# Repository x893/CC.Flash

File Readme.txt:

Implement Texas flash programming protocol via Arduino board.
See
http://www.ti.com/tool/cc-debugger
and
http://akb77.com/g/rf/program-cc-debugger-cc2511-with-arduino/
for details

1. Upload CC_Flash.pde sketch to Arduino
2. Connect
    Target          Arduino
        DC (P2.1) - pin 5
        DD (P2.2) - pin 6
        RST       - pin 7
        GND       - GND
3. Start program CC.Flash.exe (need .NET 2.0)

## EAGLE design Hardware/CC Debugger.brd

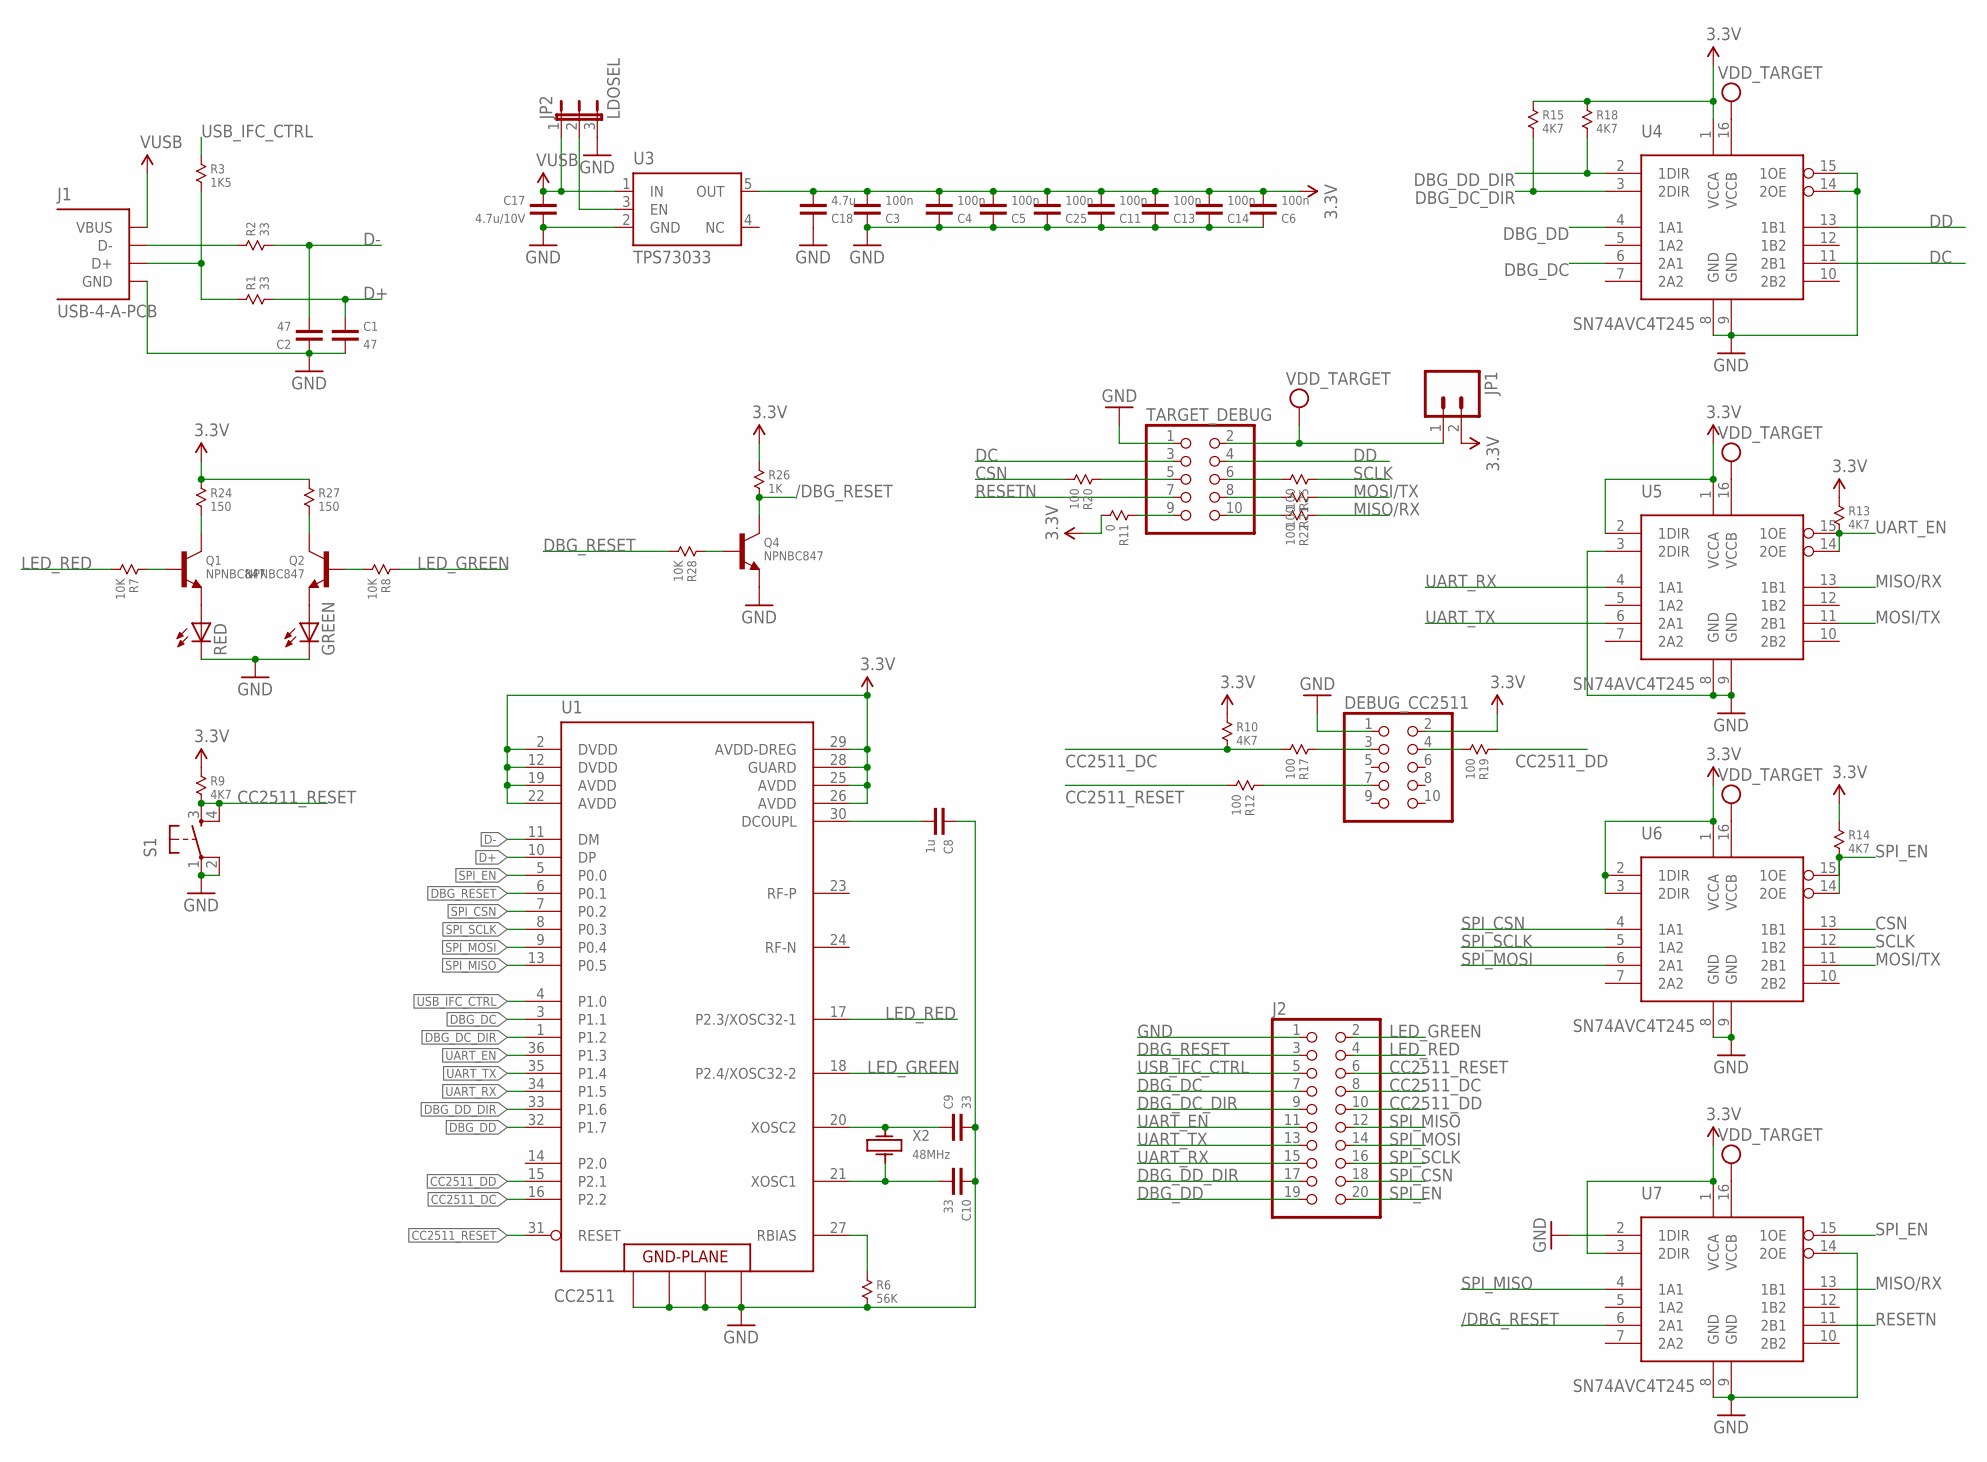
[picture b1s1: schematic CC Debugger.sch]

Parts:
C1, C2: 47; 0603
C3, C4, C5, C6, C11, C13, C14, C25: 100n; 0603
C8: 1u; 0603
C9, C10: 33; 0603
C17: 4.7u/10V; 0603
C18: 4.7u; 0603
DEBUG_CC2511: PINHD-2X5; 2X05
GREEN: LEDCHIPLED_0805; CHIPLED_0805
J1: USB-4-A-PCB; USB-A-PCB
J2: PINHD-2X10; 2X10
JP1: M02PTH; 1X02
JP2: LDOSEL; SJ_3
Q1, Q2, Q4: NPNBC847; SOT-23
R1, R2: 33; 0603
R3: 1K5; 0603
R6: 56K; 0603
R7, R8, R28: 10K; 0603
R9, R10, R13, R14, R15, R18: 4K7; 0603
R11: 0; 0603
R12, R17, R19, R20, R21, R22, R25: 100; 0603
R24, R27: 150; 0603
R26: 1K; 0603
RED: LEDCHIPLED_0805; CHIPLED_0805
S1: TAC_SWITCHPTH; TACTILE-PTH
TARGET_DEBUG: PINHD-2X5; 2X05
U1: CC2511; QLP-36
U3: TPS73033; SOT23-5
U4, U5, U6, U7: SN74AVC4T245; TSSOP16
X2: 48MHz; KX-9A

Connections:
3.3V: C3.1, C4.1, C5.1, C6.1, C11.1, C13.1, C14.1, C18.1, C25.1, DEBUG_CC2511.2, JP1.2, R9.1, R10.1, R11.2, R13.1, R14.1, R15.1, R18.1, R24.1, R26.1, R27.1, U1.2 (DVDD), U1.12 (DVDD), U1.19 (AVDD), U1.22 (AVDD), U1.25 (AVDD), U1.26 (AVDD), U1.28 (GUARD), U1.29 (AVDD-DREG), U3.5 (OUT), U4.1 (VCCA), U5.1 (VCCA), U5.2 (1DIR), U6.1 (VCCA), U6.2 (1DIR), U6.3 (2DIR), U7.1 (VCCA), U7.3 (2DIR)
5V: C17.2, J1.VUSB (VBUS), JP2.1, U3.1 (IN)
/DBG_RESET: Q4.3 (C), R26.2, U7.6 (2A1)
CC2511_DC: J2.8, R10.2, R17.2, U1.16 (P2.2)
CC2511_DD: J2.10, R19.1, U1.15 (P2.1)
CC2511_RESET: J2.6, R9.2, R12.2, S1.3, S1.4, U1.31 (RESET)
CSN: R20.2, U6.13 (1B1)
D+: C1.2, R1.2, U1.10 (DP)
D-: C2.1, R2.2, U1.11 (DM)
DBG_DC: J2.7, U1.3 (P1.1), U4.6 (2A1)
DBG_DC_DIR: J2.9, R15.2, U1.1 (P1.2), U4.3 (2DIR)
DBG_DD: J2.19, U1.32 (P1.7), U4.4 (1A1)
DBG_DD_DIR: J2.17, R18.2, U1.33 (P1.6), U4.2 (1DIR)
DBG_RESET: J2.3, R28.2, U1.6 (P0.1)
DC: TARGET_DEBUG.3, U4.11 (2B1)
DD: TARGET_DEBUG.4, U4.13 (1B1)
GND: C1.1, C2.2, C3.2, C4.2, C5.2, C6.2, C8.2, C9.1, C10.2, C11.2, C13.2, C14.2, C17.1, C18.2, C25.2, DEBUG_CC2511.1, GREEN.C, J1.GND, J2.1, JP2.3, Q4.2 (E), R6.2, RED.C, S1.1, S1.2, TARGET_DEBUG.1, U1.37 (GND), U1.38 (GND), U1.39 (GND), U1.40 (GND), U3.2 (GND), U4.8 (GND), U4.9 (GND), U4.14 (2OE), U4.15 (1OE), U5.3 (2DIR), U5.8 (GND), U5.9 (GND), U6.8 (GND), U6.9 (GND), U7.2 (1DIR), U7.8 (GND), U7.9 (GND), U7.14 (2OE)
LED_GREEN: J2.2, R8.1, U1.18 (P2.4/XOSC32-2)
LED_RED: J2.4, R7.2, U1.17 (P2.3/XOSC32-1)
MISO/RX: R22.1, U5.13 (1B1), U7.13 (1B1)
MOSI/TX: R21.1, U5.11 (2B1), U6.11 (2B1)
unnamed: J1.D-, R2.1
unnamed: J1.D+, R1.1, R3.2
unnamed: GREEN.A, Q2.2 (E)
unnamed: Q1.2 (E), RED.A
unnamed: Q2.3 (C), R27.2
unnamed: Q1.3 (C), R24.2
unnamed: Q2.1 (B), R8.2
unnamed: DEBUG_CC2511.3, R17.1
unnamed: Q1.1 (B), R7.1
unnamed: DEBUG_CC2511.7, R12.1
unnamed: DEBUG_CC2511.4, R19.2
unnamed: R25.2, TARGET_DEBUG.6
unnamed: C9.2, U1.20 (XOSC2), X2.1
unnamed: R21.2, TARGET_DEBUG.8
unnamed: R22.2, TARGET_DEBUG.10
unnamed: C10.1, U1.21 (XOSC1), X2.3 (2)
unnamed: R6.1, U1.27 (RBIAS)
unnamed: C8.1, U1.30 (DCOUPL)
unnamed: R11.1, TARGET_DEBUG.9
unnamed: R20.1, TARGET_DEBUG.5
unnamed: Q4.1 (B), R28.1
unnamed: JP2.2, U3.3 (EN)
RESETN: TARGET_DEBUG.7, U7.11 (2B1)
SCLK: R25.1, U6.12 (1B2)
SPI_CSN: J2.18, U1.7 (P0.2), U6.4 (1A1)
SPI_EN: J2.20, R14.2, U1.5 (P0.0), U6.14 (2OE), U6.15 (1OE), U7.15 (1OE)
SPI_MISO: J2.12, U1.13 (P0.5), U7.4 (1A1)
SPI_MOSI: J2.14, U1.9 (P0.4), U6.6 (2A1)
SPI_SCLK: J2.16, U1.8 (P0.3), U6.5 (1A2)
UART_EN: J2.11, R13.2, U1.36 (P1.3), U5.14 (2OE), U5.15 (1OE)
UART_RX: J2.15, U1.34 (P1.5), U5.4 (1A1)
UART_TX: J2.13, U1.35 (P1.4), U5.6 (2A1)
USB_IFC_CTRL: J2.5, R3.1, U1.4 (P1.0)
VDD: JP1.1, TARGET_DEBUG.2, U4.16 (VCCB), U5.16 (VCCB), U6.16 (VCCB), U7.16 (VCCB)

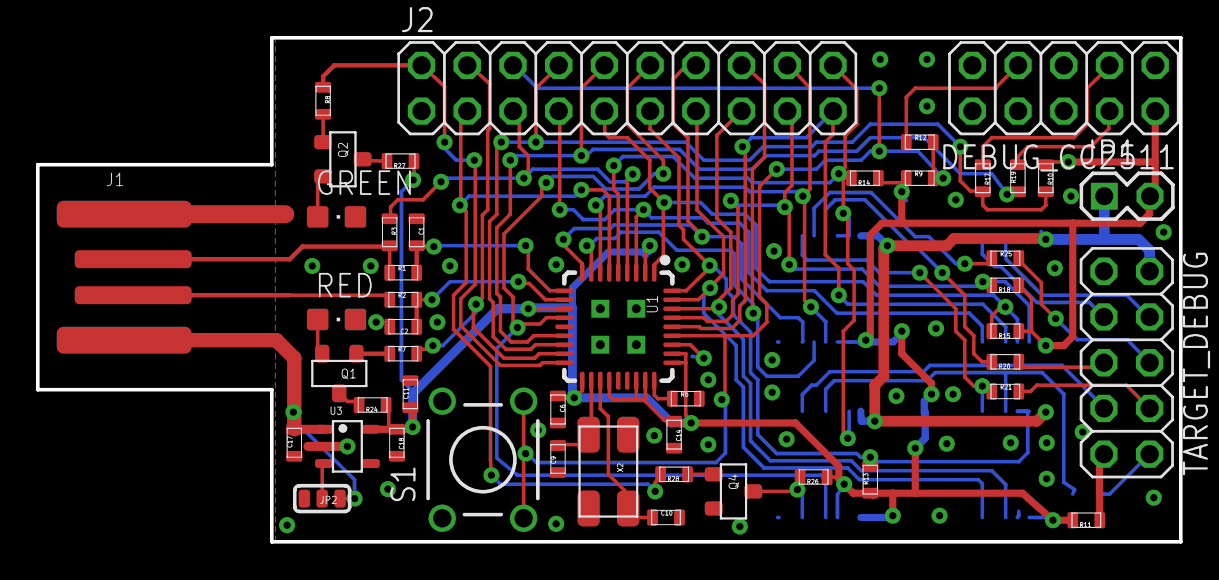
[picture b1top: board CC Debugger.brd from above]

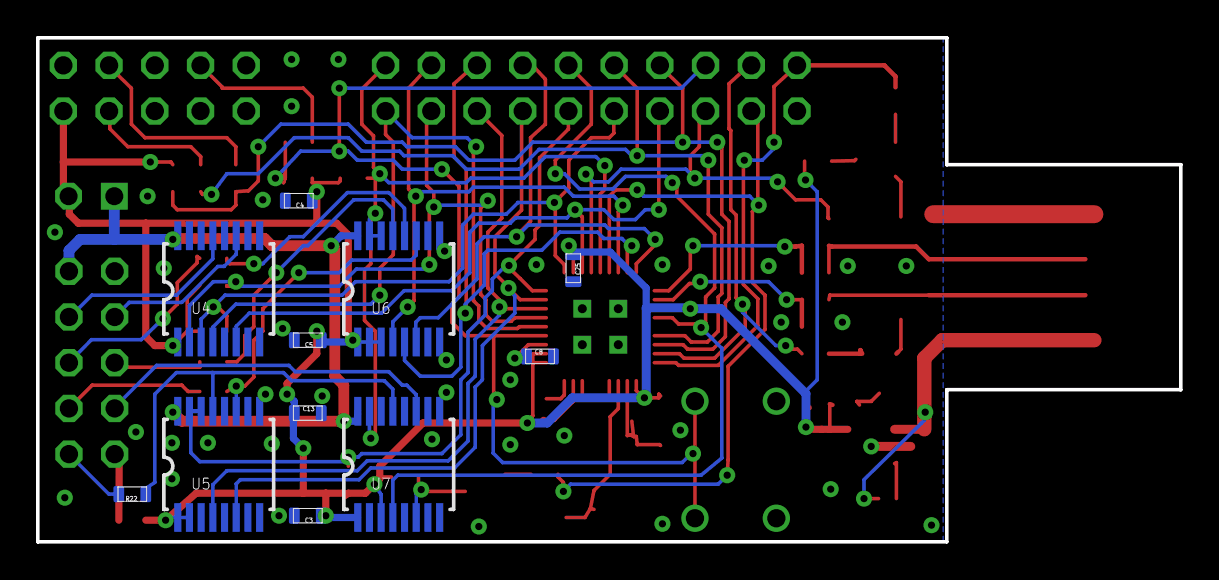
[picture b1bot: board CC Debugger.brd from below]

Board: 2 copper layers, 63.5 x 28.0 mm, 58 parts (11 on the bottom side), 55 nets.

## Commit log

2013-02-03 Initial
2013-02-03 Change Readme
2013-02-03 Add execution files
2013-02-03 Fix Readme
2013-02-03 Fixes CC.Flash project
2013-02-08 Add hardware files for Eagle 6
2018-09-15 Fix the bug where the controls were never enabled (even after a successful connection)
2018-09-15 Add .bat file to make it easier to compile without Visual Studio installed
2018-09-15 Switch to FastGPIO for faster performance (particularly noticable on reads)
2018-09-22 Added Button for sending Chip Erase (for clearing lock bits)
2018-09-24 Major performance optimizations and Arduino Sketch code refactor to make it easier to follow
2018-09-25 increase baudrate to 250000, and replace Serial.print(num, HEX) with much faster version.
2018-09-25 Add time taken to write/read and prompt some error messages
2018-09-25 increase baudrate to 500000 and increase packet size to 120
2018-10-04 Start introducing support for Gen2 CC25xx MCUs (flash read works)
2018-10-04 Add flash write support for Gen2 CC25xx MCUs
2018-10-04 minor tweak
2018-10-04 new executable
2018-10-04 formatting
